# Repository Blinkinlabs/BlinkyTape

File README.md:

# BlinkyTape

BlinkyTape is a one meter long, full-color light tape with 60 independent RGB LEDs controlled by our custom light processor. Power and communications are provided by a built-in micro-USB connector. An on-board button allows for simple interactions such as choosing between effects.

BlinkyTape is flexible, so you can easily integrate it into any shape your project needs. BlinkyTape also comes enclosed in weatherproof silicone, so it's suitable for outdoor use!

This GitHub repository contains the design files for the BlinkyTape controller, as well as the production test files.

More information about the BlinkyTape is available here: [http://blinkinlabs.com/blinkytape/](http://blinkinlabs.com/blinkytape/)

# I want one!

Cool! BlinkyTape is available in [our store](http://blinkinlabs.myshopify.com/products/blinkytape-basic), as well as through many fine distributors.

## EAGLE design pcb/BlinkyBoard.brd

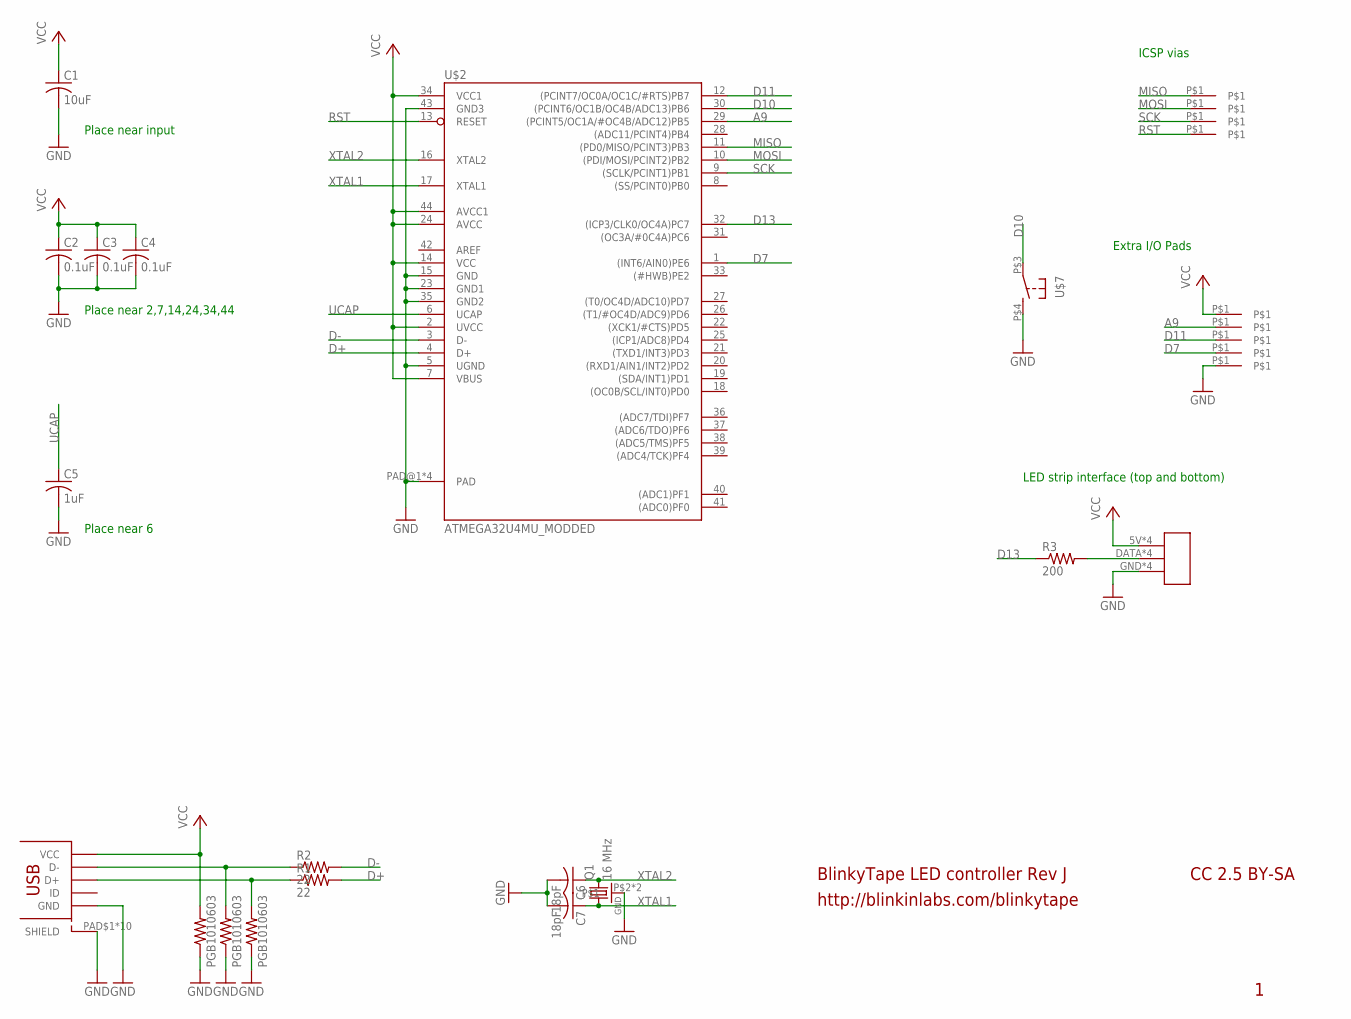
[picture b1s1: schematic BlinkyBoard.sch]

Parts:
C1: 10uF; C0603K
C2, C3, C4: 0.1uF; CAP_0402_KEMET_MEDIAN
C5: 1uF; CAP_0402_KEMET_MEDIAN
C6, C7: 18pF; CAP_0402_KEMET_MEDIAN
Q1: 16 MHz; CRSYTAL_2520
R1, R2: 22; RES_0402_KEMET_MEDIAN
R3: 200; RES_0402_KEMET_MEDIAN
U$1, U$3, U$5, U$6: TEST_PAD_SMT; TEST_PAD_1MM
U$2: ATMEGA32U4MU_MODDED; QFN44ML_7X7_LONGLEADS_MOD
U$4: USB_MICROSMT+THRUHULE; USB_MICRO_THRUHOLE
U$7: BUTTON_MOMENTARY; BUTTON_2P_SMD
U$9: WS2812B_CONNECTOR
U$10, U$11, U$12, U$13, U$14: TEST_PAD_SMT
Z1, Z2, Z3: PGB1010603; SPARKFUN-RESISTORS_0603-RES; MPN PGB1010603NRHF

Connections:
A9: U$2.29 ((PCINT5/OC1A/#OC4B/ADC12)PB5), U$11.P$1
AREF: U$2.42 (AREF)
D7: U$2.1 ((INT6/AIN0)PE6), U$10.P$1
D10: U$2.30 ((PCINT6/OC1B/OC4B/ADC13)PB6), U$7.P$3
D11: U$2.12 ((PCINT7/OC0A/OC1C/#RTS)PB7), U$14.P$1
D13: R3.P$1 (1), U$2.32 ((ICP3/CLK0/OC4A)PC7)
D+: R1.P$2 (2), U$2.4 (D+)
D+_IN: R1.P$1 (1), U$4.PIN$3 (D+), Z1.2
D-: R2.P$2 (2), U$2.3 (D-)
D-_IN: R2.P$1 (1), U$4.PIN$2 (D-), Z2.2
GND: C1.2, C2.P$2 (2), C3.P$2 (2), C4.P$2 (2), C5.P$2 (2), C6.P$2 (2), C7.P$2 (2), Q1.P$2, Q1.P$4, U$2.5 (UGND), U$2.15 (GND), U$2.23 (GND1), U$2.35 (GND2), U$2.43 (GND3), U$2.PAD@1 (PAD), U$2.PAD@4 (PAD), U$2.PAD@13 (PAD), U$2.PAD@16 (PAD), U$4.PAD$1 (SHIELD), U$4.PAD$2 (SHIELD), U$4.PAD$3 (SHIELD), U$4.PAD$4 (SHIELD), U$4.PAD$5 (SHIELD), U$4.PAD$6 (SHIELD), U$4.PAD$7 (SHIELD), U$4.PAD$8 (SHIELD), U$4.PAD$9 (SHIELD), U$4.PAD$10 (SHIELD), U$4.PIN$5 (GND), U$7.P$4 (S), U$9.GND, U$9.GND1 (GND), U$9.GND_1 (GND), U$9.GND_2 (GND), U$13.P$1, Z1.1, Z2.1, Z3.1
LED_DATA: R3.P$2 (2), U$9.DATA, U$9.DATA1 (DATA), U$9.DATA_1 (DATA), U$9.DATA_2 (DATA)
MISO: U$1.P$1, U$2.11 ((PD0/MISO/PCINT3)PB3)
MOSI: U$2.10 ((PDI/MOSI/PCINT2)PB2), U$3.P$1
RST: U$2.13 (RESET), U$6.P$1
SCK: U$2.9 ((SCLK/PCINT1)PB1), U$5.P$1
UCAP: C5.P$1 (1), U$2.6 (UCAP)
VCC: C1.1, C2.P$1 (1), C3.P$1 (1), C4.P$1 (1), U$2.2 (UVCC), U$2.7 (VBUS), U$2.14 (VCC), U$2.24 (AVCC), U$2.34 (VCC1), U$2.44 (AVCC1), U$4.PIN$1 (VCC), U$9.5V, U$9.5V1 (5V), U$9.5V_1 (5V), U$9.5V_2 (5V), U$12.P$1, Z3.2
XTAL1: C7.P$1 (1), Q1.P$1 (1), U$2.17 (XTAL1)
XTAL2: C6.P$1 (1), Q1.P$3 (2), U$2.16 (XTAL2)

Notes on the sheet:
BlinkyTape LED controller Rev J
http://blinkinlabs.com/blinkytape
CC 2.5 BY-SA
ICSP vias
Extra I/O Pads
LED strip interface (top and bottom)
Place near 6
Place near 2,7,14,24,34,44
Place near input

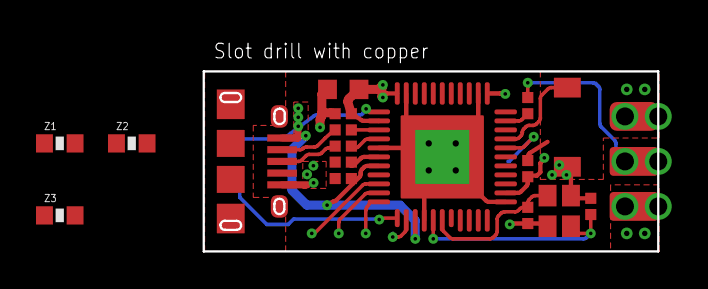
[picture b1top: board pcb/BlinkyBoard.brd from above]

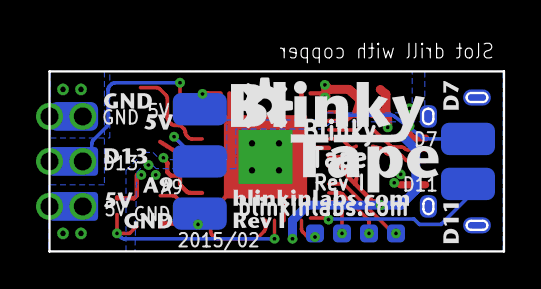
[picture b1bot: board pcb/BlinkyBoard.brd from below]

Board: 2 copper layers, 25.2 x 10.0 mm, 28 parts (11 on the bottom side), 19 nets.

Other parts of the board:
U$15: OSHW-LOGO-S

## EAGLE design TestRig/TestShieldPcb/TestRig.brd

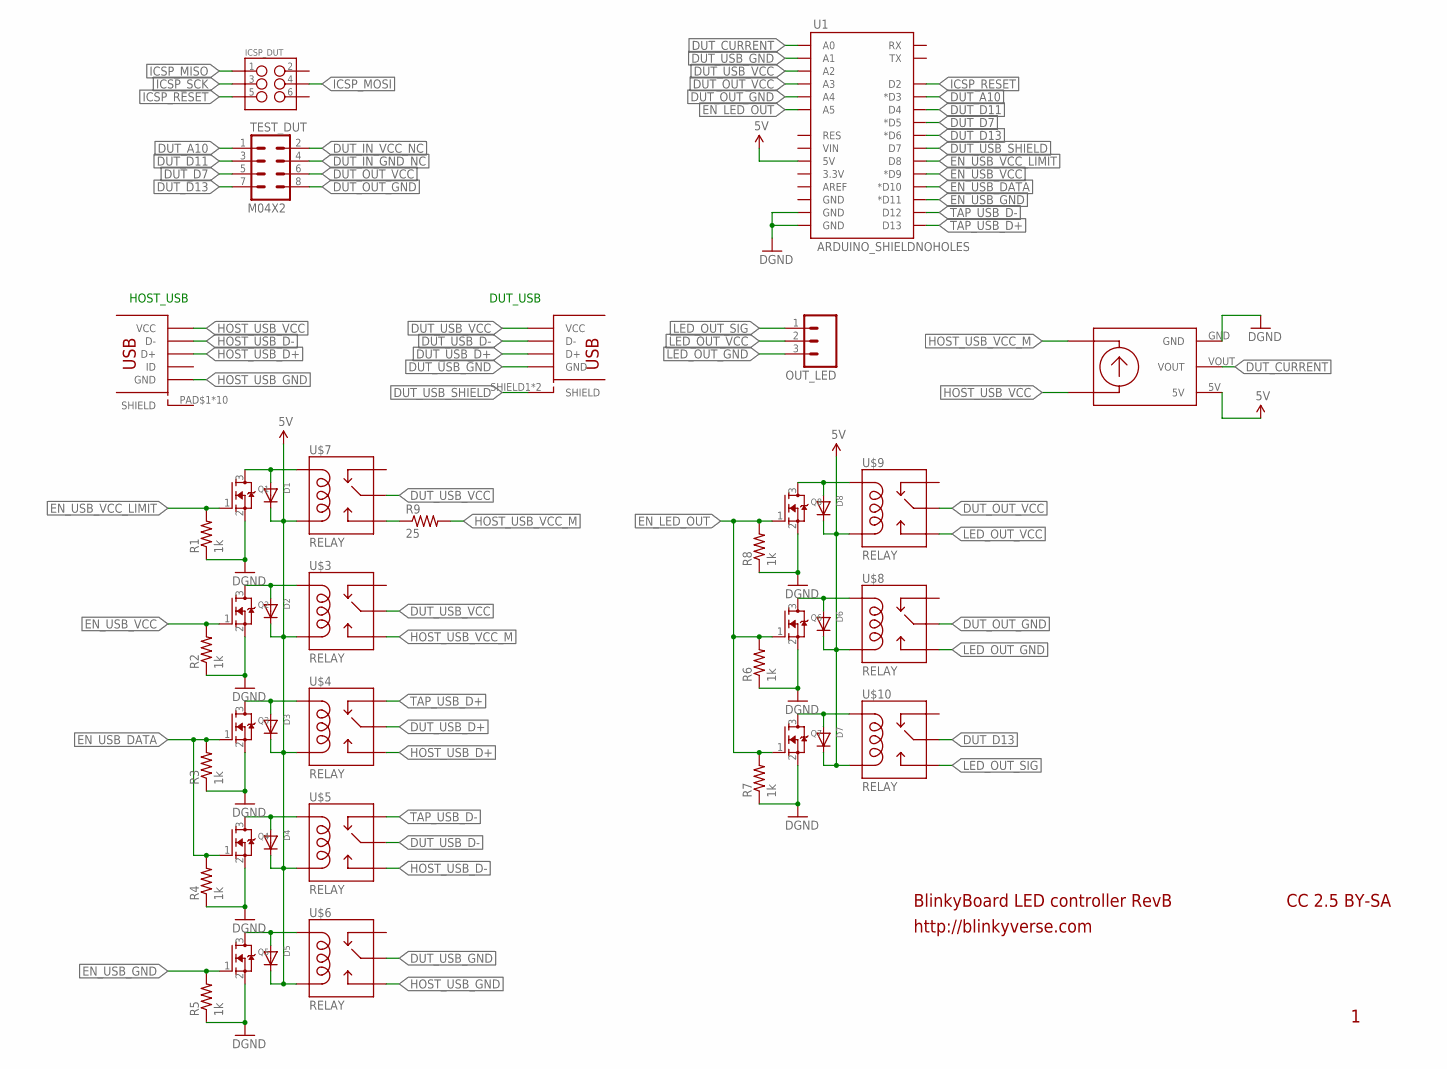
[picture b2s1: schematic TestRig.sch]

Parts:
D1, D2, D3, D4, D5, D6, D7, D8: DIODESOD-523; SOD-523
ICSP_DUT: M03X2NO_SILK; 2X3-NS
OUT_LED: M03PTH; 1X03
Q1, Q2, Q3, Q4, Q5, Q6, Q7, Q8: MOSFET-NREFLOW; SOT23
R1, R2, R3, R4, R5, R6, R7, R8: 1k; R0603
R9: 25; R1210
TEST_DUT: M04X2; 2X4
U1: ARDUINO_SHIELDNOHOLES; DUEMILANOVE_SHIELD_NOHOLES
U$1: USB; USB_A_FEMALE_NOSILK_SHIELD
U$2: MICRO_USBSMT+THRUHULE; MICRO_USB_FCI_THRUHOLE
U$3, U$4, U$5, U$6, U$7, U$8, U$9, U$10: RELAY; RELAY_HK23F-5V
U$11: SPARKFUN_ACS712

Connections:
5V: D1.K (C), D2.K (C), D3.K (C), D4.K (C), D5.K (C), D6.K (C), D7.K (C), D8.K (C), U1.5V, U$3.P$5 (COIL2), U$4.P$5 (COIL2), U$5.P$5 (COIL2), U$6.P$5 (COIL2), U$7.P$5 (COIL2), U$8.P$5 (COIL2), U$9.P$5 (COIL2), U$10.P$5 (COIL2), U$11.5V
DUT_A10: TEST_DUT.1, U1.D3 (*D3)
DUT_CURRENT: U1.A0, U$11.VOUT
DUT_D7: TEST_DUT.5, U1.D5 (*D5)
DUT_D11: TEST_DUT.3, U1.D4
DUT_D13: TEST_DUT.7, U1.D6 (*D6), U$10.P$1 (MAIN), U$10.P$6 (MAIN)
DUT_IN_GND_NC: TEST_DUT.4
DUT_IN_VCC_NC: TEST_DUT.2
DUT_OUT_GND: TEST_DUT.8, U1.A4, U$8.P$1 (MAIN), U$8.P$6 (MAIN)
DUT_OUT_VCC: TEST_DUT.6, U1.A3, U$9.P$1 (MAIN), U$9.P$6 (MAIN)
DUT_USB_D+: U$1.D+, U$4.P$1 (MAIN), U$4.P$6 (MAIN)
DUT_USB_D-: U$1.D-, U$5.P$1 (MAIN), U$5.P$6 (MAIN)
DUT_USB_GND: U1.A1, U$1.GND, U$6.P$1 (MAIN), U$6.P$6 (MAIN)
DUT_USB_SHIELD: U1.D7, U$1.SHIELD1 (SHIELD), U$1.SHIELD2 (SHIELD)
DUT_USB_VCC: U1.A2, U$1.VBUS (VCC), U$3.P$1 (MAIN), U$3.P$6 (MAIN), U$7.P$1 (MAIN), U$7.P$6 (MAIN)
EN_LED_OUT: Q6.1 (G), Q7.1 (G), Q8.1 (G), R6.2, R7.2, R8.2, U1.A5
EN_USB_DATA: Q3.1 (G), Q4.1 (G), R3.2, R4.2, U1.D10 (*D10)
EN_USB_GND: Q5.1 (G), R5.2, U1.D11 (*D11)
EN_USB_VCC: Q2.1 (G), R2.2, U1.D9 (*D9)
EN_USB_VCC_LIMIT: Q1.1 (G), R1.2, U1.D8
GND: Q1.2 (S), Q2.2 (S), Q3.2 (S), Q4.2 (S), Q5.2 (S), Q6.2 (S), Q7.2 (S), Q8.2 (S), R1.1, R2.1, R3.1, R4.1, R5.1, R6.1, R7.1, R8.1, U1.GND@0 (GND), U1.GND@1 (GND), U$11.GND
HOST_USB_D+: U$2.PIN$3 (D+), U$4.P$3 (NO)
HOST_USB_D-: U$2.PIN$2 (D-), U$5.P$3 (NO)
HOST_USB_GND: U$2.PIN$5 (GND), U$6.P$3 (NO)
HOST_USB_VCC: U$2.PIN$1 (VCC), U$11.IP-
HOST_USB_VCC_M: R9.2, U$3.P$3 (NO), U$11.IP+
ICSP_MISO: ICSP_DUT.1
ICSP_MOSI: ICSP_DUT.4
ICSP_RESET: ICSP_DUT.5, U1.D2
ICSP_SCK: ICSP_DUT.3
LED_OUT_GND: OUT_LED.3, U$8.P$3 (NO)
LED_OUT_SIG: OUT_LED.1, U$10.P$3 (NO)
LED_OUT_VCC: OUT_LED.2, U$9.P$3 (NO)
unnamed: R9.1, U$7.P$3 (NO)
unnamed: D1.A, Q1.3 (D), U$7.P$2 (COIL1)
unnamed: D2.A, Q2.3 (D), U$3.P$2 (COIL1)
unnamed: D3.A, Q3.3 (D), U$4.P$2 (COIL1)
unnamed: D4.A, Q4.3 (D), U$5.P$2 (COIL1)
unnamed: D5.A, Q5.3 (D), U$6.P$2 (COIL1)
unnamed: D6.A, Q6.3 (D), U$8.P$2 (COIL1)
unnamed: D7.A, Q7.3 (D), U$10.P$2 (COIL1)
unnamed: D8.A, Q8.3 (D), U$9.P$2 (COIL1)
TAP_USB_D+: U1.D13, U$4.P$4 (NC)
TAP_USB_D-: U1.D12, U$5.P$4 (NC)

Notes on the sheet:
BlinkyBoard LED controller RevB
http://blinkyverse.com
CC 2.5 BY-SA
DUT_USB
HOST_USB

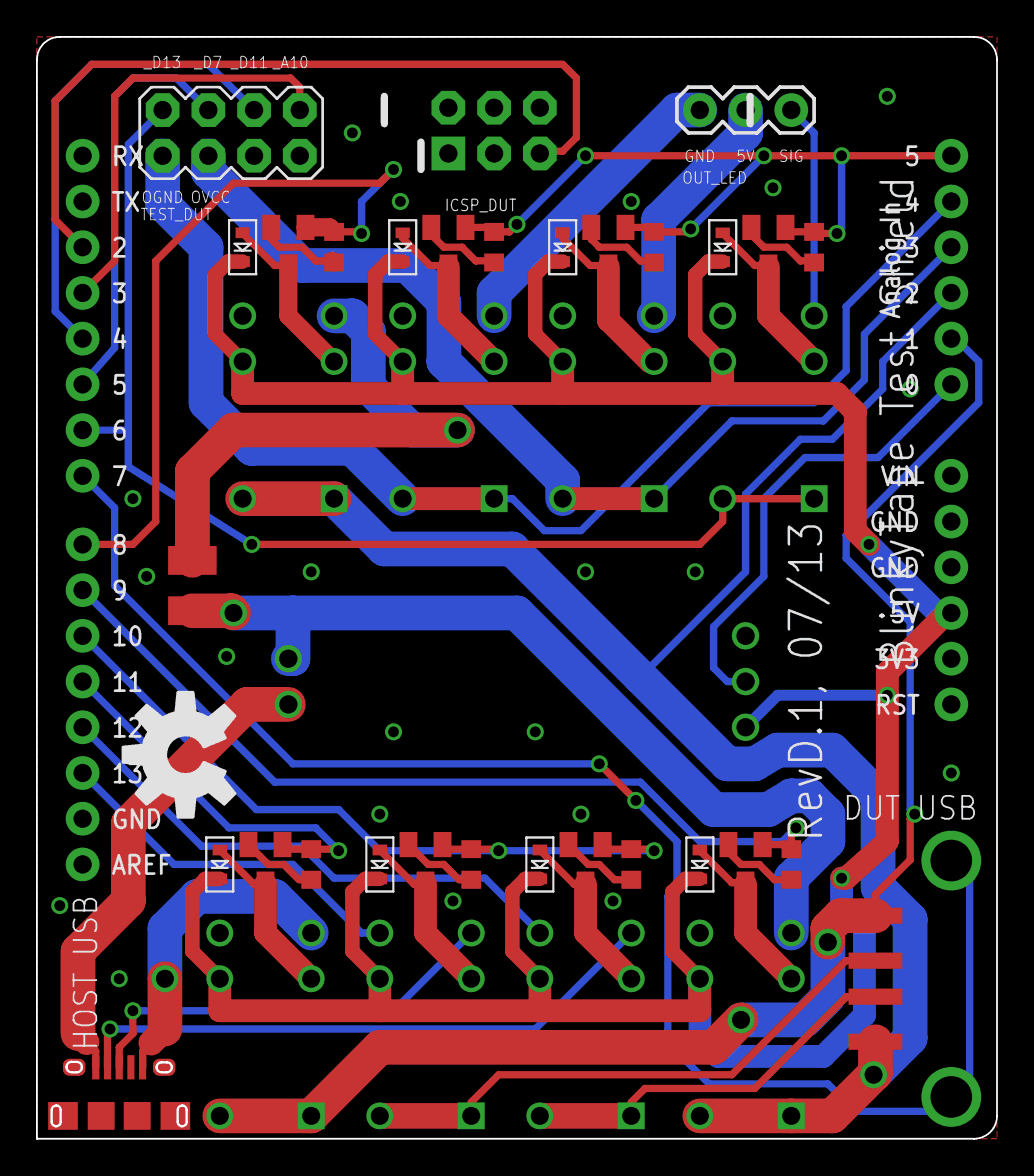
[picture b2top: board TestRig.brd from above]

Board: 2 copper layers, 53.3 x 61.2 mm, 41 parts (0 on the bottom side), 39 nets.

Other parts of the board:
U$12: OSHW-LOGO-L

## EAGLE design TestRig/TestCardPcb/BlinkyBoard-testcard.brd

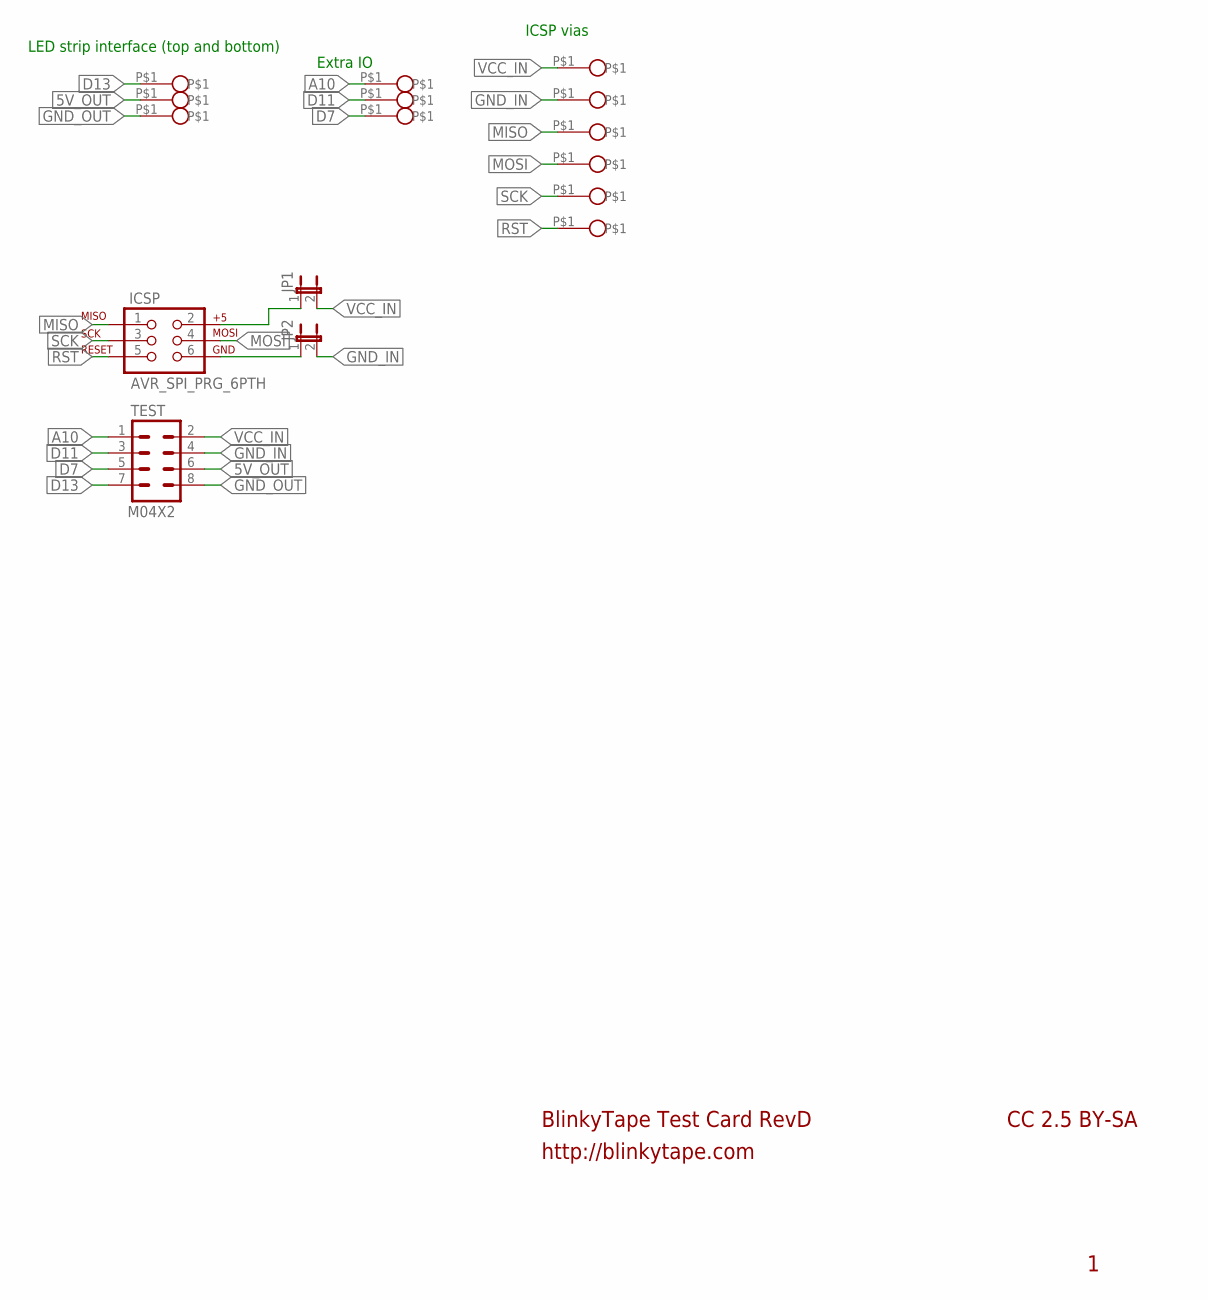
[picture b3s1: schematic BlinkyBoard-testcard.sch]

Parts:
ICSP: AVR_SPI_PRG_6PTH; 2X3
JP1, JP2: JUMPER-2PTH; 1X02
TEST: M04X2; 2X4
U$9, U$16, U$22, U$23, U$24, U$26, U$27, U$28: POGO_PIN; POGO_PIN_1MM
U$17, U$18, U$19, U$20: POGO_PINOBLONG; POGO_PIN_1MM_OBLONG

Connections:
5V_OUT: TEST.6, U$27.P$1
A10: TEST.1, U$22.P$1
D7: TEST.5, U$24.P$1
D11: TEST.3, U$23.P$1
D13: TEST.7, U$26.P$1
GND_IN: JP2.2, TEST.4, U$16.P$1
GND_OUT: TEST.8, U$28.P$1
MISO: ICSP.1, U$17.P$1
MOSI: ICSP.4, U$18.P$1
unnamed: ICSP.2, JP1.1
unnamed: ICSP.6, JP2.1
RST: ICSP.5, U$20.P$1
SCK: ICSP.3, U$19.P$1
VCC_IN: JP1.2, TEST.2, U$9.P$1

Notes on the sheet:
BlinkyTape Test Card RevD
http://blinkytape.com
CC 2.5 BY-SA
ICSP vias
LED strip interface (top and bottom)
Extra IO

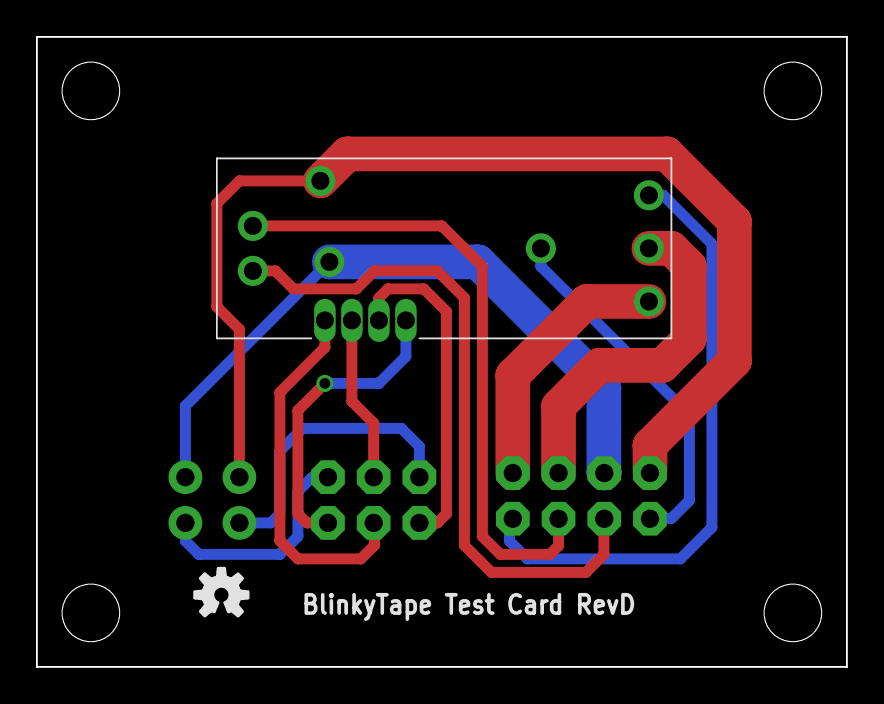
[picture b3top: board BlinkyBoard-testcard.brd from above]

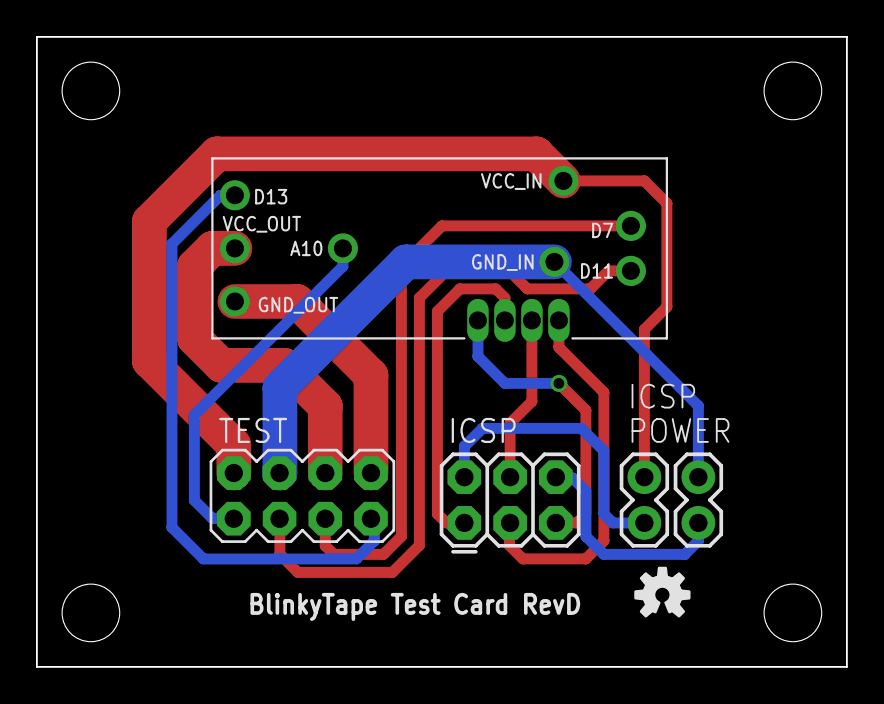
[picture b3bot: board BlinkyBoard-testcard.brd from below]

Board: 2 copper layers, 45.0 x 35.0 mm, 18 parts (5 on the bottom side), 14 nets.

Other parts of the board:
U$3, U$15: OSHW-LOGO-S

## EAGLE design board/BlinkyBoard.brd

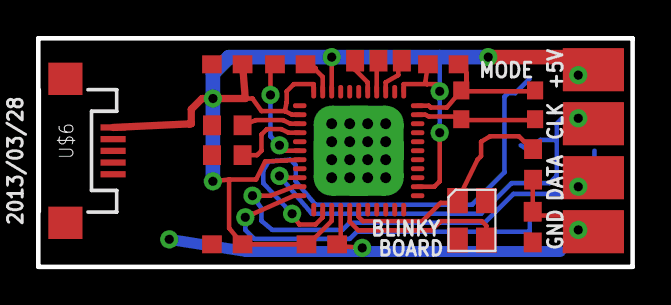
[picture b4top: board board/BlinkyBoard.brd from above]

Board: 2 copper layers, 33.0 x 12.7 mm, 17 parts (0 on the bottom side), 17 nets.

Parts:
C1: 1uF; C0603
C2, C3: 18pF; C0603
C4, C6, C7, C8: 0.1uF; C0603
Q1: 16 MHz; XS3225
R1, R2: 22; R0603
S1: Normally open; GLOWBOARD_KMR211G_SWITCH
U$1: ARDUINO_LEONARDO-REV3B_SMARTPRJ_ATMEGA32U4-XUMU; ARDUINO_LEONARDO-REV3B_SMARTPRJ_QFN44ML7X7
U$2: GLOWBOARD_USB_TEST_PADS
U$3: GLOWBOARD_PAD_CONNECTION
U$4: GLOWBOARD_ICSP; GLOWBOARD_ICSP_PADS
U$5: GLOWBOARD_EXPANSION_HEADER
U$6: USB-MICROB

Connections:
+3V3: C1.1, U$1.6
D+: R2.2, U$1.4
D+_IN: R2.1, U$2.D+, U$6.D+
D-: R1.2, U$1.3
D-_IN: R1.1, U$2.D-, U$6.D-
GND: C1.2, C2.2, C3.2, C4.2, C6.2, C7.2, C8.2, S1.P$1, S1.P$2, U$1.5, U$1.15, U$1.23, U$1.33, U$1.35, U$1.43, U$1.PAD@1, U$1.PAD@2, U$1.PAD@3, U$1.PAD@4, U$1.PAD@5, U$1.PAD@6, U$1.PAD@7, U$1.PAD@8, U$1.PAD@9, U$1.PAD@10, U$1.PAD@11, U$1.PAD@12, U$1.PAD@13, U$1.PAD@14, U$1.PAD@15, U$1.PAD@16, U$3.GND, U$4.GND, U$6.GND
MISO: U$1.11, U$4.MISO
MOSI: U$1.10, U$3.DATA, U$4.MOSI
unnamed: U$1.38, U$5.P$1
unnamed: U$1.37, U$5.P$2
unnamed: U$1.36, U$5.P$3
unnamed: C2.1, Q1.P$3, U$1.16
unnamed: C3.1, Q1.P$1, U$1.17
unnamed: S1.P$3, S1.P$4, U$1.32
RST: U$1.13, U$4.RST
SCK: U$1.9, U$3.CLK, U$4.SCK
VCC: C4.1, C6.1, C7.1, C8.1, U$1.2, U$1.7, U$1.14, U$1.24, U$1.34, U$1.42, U$1.44, U$3.+5V, U$4.VCC, U$6.VBUS

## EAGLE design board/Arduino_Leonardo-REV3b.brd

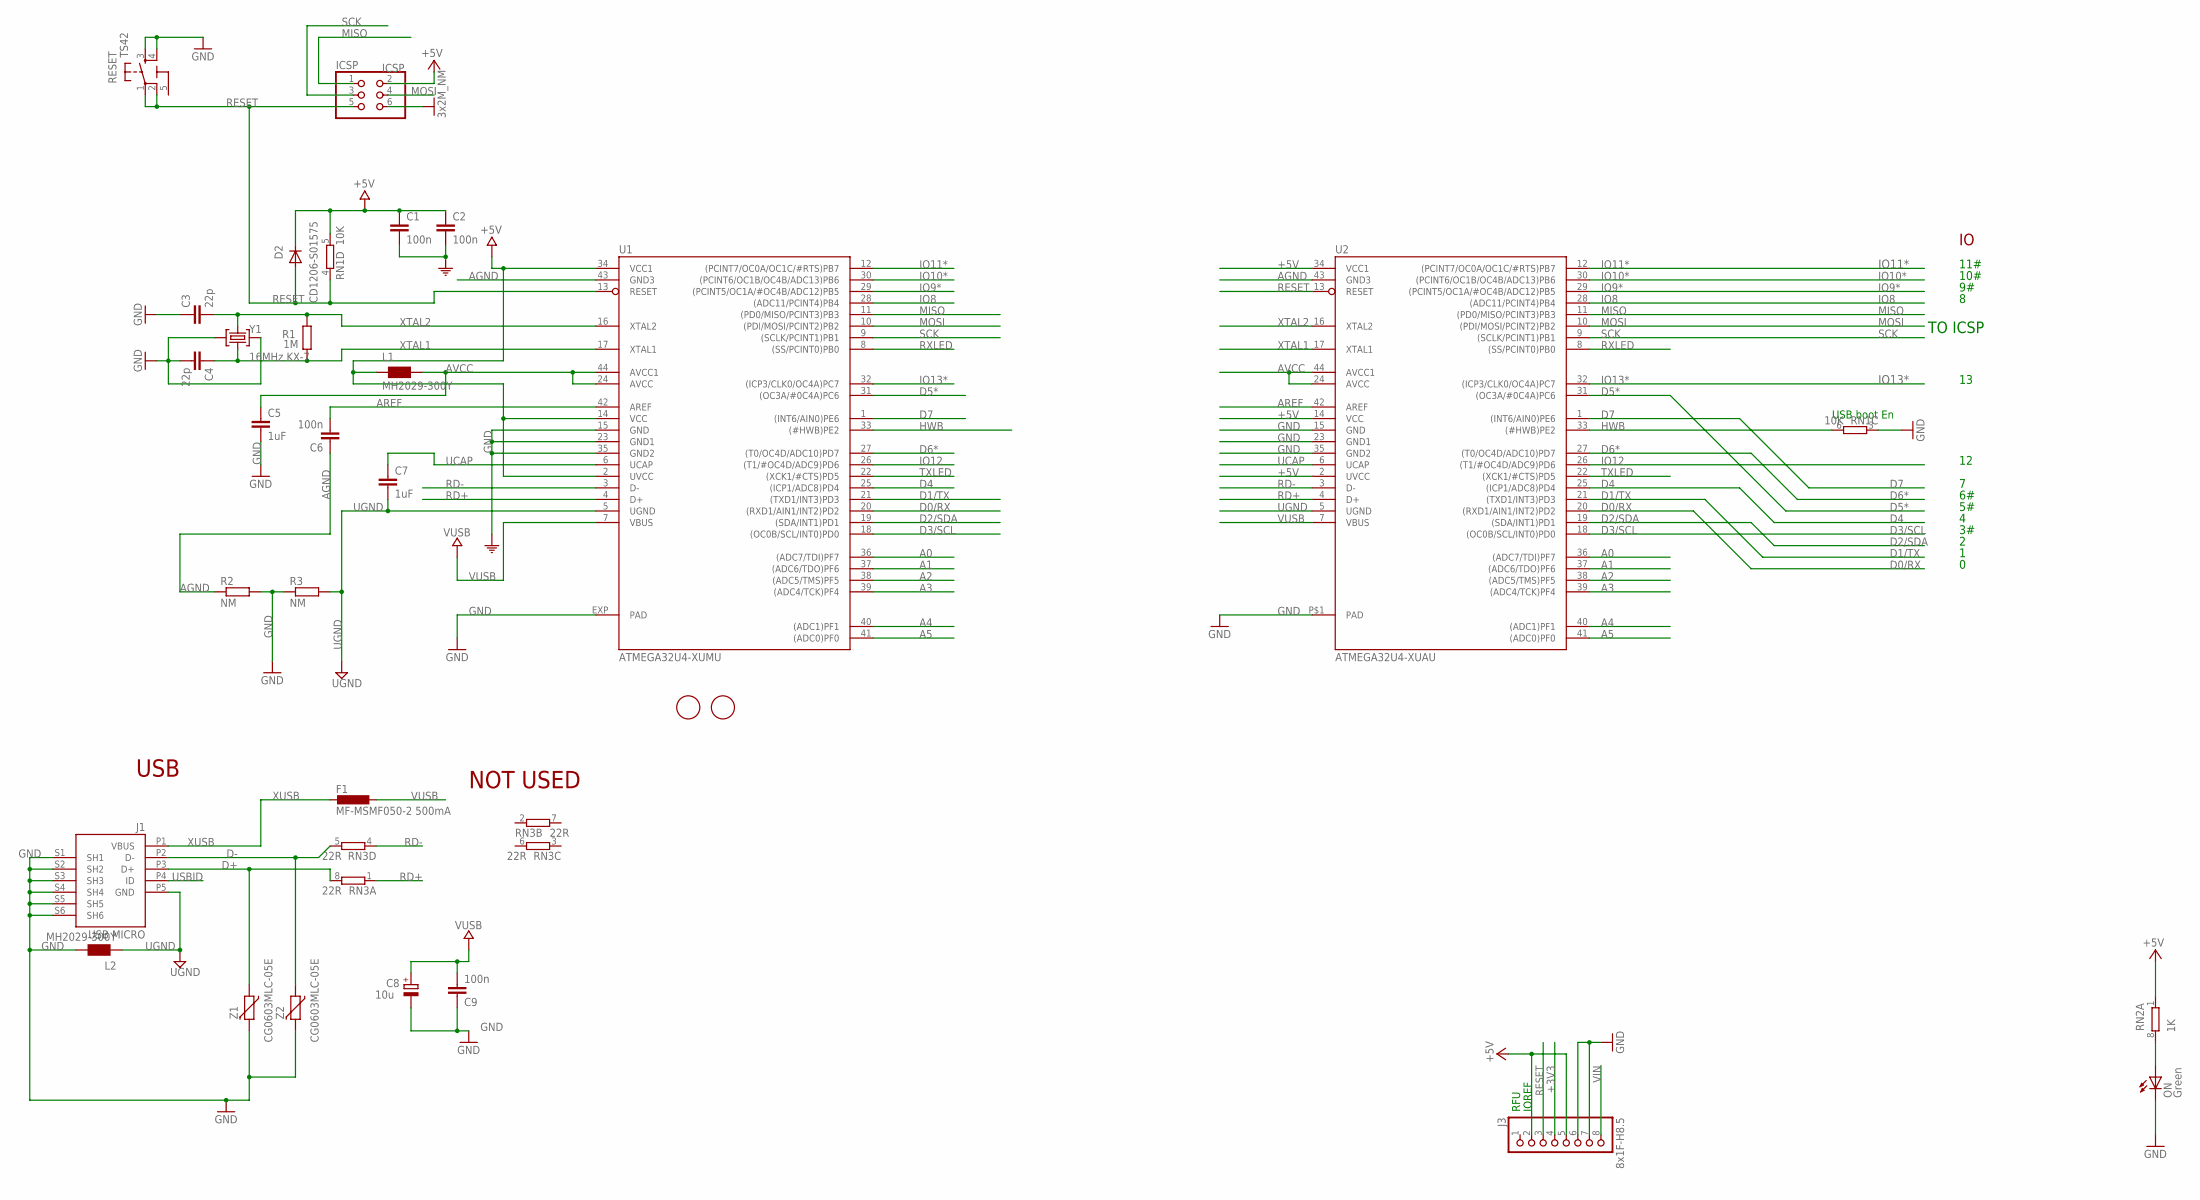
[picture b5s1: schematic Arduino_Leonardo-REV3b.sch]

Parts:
C1, C2, C6, C9: 100n; C0603-ROUND
C3, C4: 22p; C0603-ROUND
C5, C7: 1uF; C0603-ROUND
C8: 10u; SMC_B
D2: CD1206-S01575; MINIMELF
F1: MF-MSMF050-2 500mA; L1812
FID1, FID2: FIDUCIALMOUNT; FIDUCIA-MOUNT
ICSP: ICSP; 2X03
J1: USB MICRO; CON2_USB_MICRO_B_AT
J3: 8x1F-H8.5; 1X08
L1, L2: MH2029-300Y; 0805
ON: Green; CHIPLED_0805
R1: 1M; R0603-ROUND
R2, R3: NM; R0402
RESET: TS42
RN1: 10K; CAY16
RN2: 1K; CAY16
RN3: 22R; CAY16
U1: ATMEGA32U4-XUMU; QFN44ML7X7
U2: ATMEGA32U4-XUAU; TQFP44-PAD
Y1: 16MHz KX-7; CRYSTAL-3.2-2.5
Z1, Z2: CG0603MLC-05E; CT/CN0603

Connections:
5-GND: RESET.5 (5-GND)
+3V3: J3.4
+5V: C1.1, C2.1, D2.C, ICSP.2, J3.2, J3.5, L1.1, RN1.5 (2), RN2.1, U1.2 (UVCC), U1.14 (VCC), U1.34 (VCC1), U2.2 (UVCC), U2.14 (VCC), U2.34 (VCC1)
A0: U1.36 ((ADC7/TDI)PF7), U2.36 ((ADC7/TDI)PF7)
A1: U1.37 ((ADC6/TDO)PF6), U2.37 ((ADC6/TDO)PF6)
A2: U1.38 ((ADC5/TMS)PF5), U2.38 ((ADC5/TMS)PF5)
A3: U1.39 ((ADC4/TCK)PF4), U2.39 ((ADC4/TCK)PF4)
A4: U1.40 ((ADC1)PF1), U2.40 ((ADC1)PF1)
A5: U1.41 ((ADC0)PF0), U2.41 ((ADC0)PF0)
AGND: C6.1, R2.1, U1.43 (GND3), U2.43 (GND3)
AREF: C6.2, U1.42 (AREF), U2.42 (AREF)
AVCC: C5.1, L1.2, U1.24 (AVCC), U1.44 (AVCC1), U2.24 (AVCC), U2.44 (AVCC1)
D0/RX: U1.20 ((RXD1/AIN1/INT2)PD2), U2.20 ((RXD1/AIN1/INT2)PD2)
D1/TX: U1.21 ((TXD1/INT3)PD3), U2.21 ((TXD1/INT3)PD3)
D2/SDA: U1.19 ((SDA/INT1)PD1), U2.19 ((SDA/INT1)PD1)
D3/SCL: U1.18 ((OC0B/SCL/INT0)PD0), U2.18 ((OC0B/SCL/INT0)PD0)
D4: U1.25 ((ICP1/ADC8)PD4), U2.25 ((ICP1/ADC8)PD4)
D5*: U1.31 ((OC3A/#0C4A)PC6), U2.31 ((OC3A/#0C4A)PC6)
D6*: U1.27 ((T0/OC4D/ADC10)PD7), U2.27 ((T0/OC4D/ADC10)PD7)
D7: U1.1 ((INT6/AIN0)PE6), U2.1 ((INT6/AIN0)PE6)
D+: J1.P3 (D+), RN3.8 (2), Z1.1
D-: J1.P2 (D-), RN3.5 (2), Z2.1
GND: C1.2, C2.2, C3.1, C4.2, C5.2, C8.-, C9.1, ICSP.6, J1.S1 (SH1), J1.S2 (SH2), J1.S3 (SH3), J1.S4 (SH4), J1.S5 (SH5), J1.S6 (SH6), J3.6, J3.7, L2.2, ON.C, R2.2, R3.1, RESET.3, RESET.4, RN1.3 (1), U1.15 (GND), U1.23 (GND1), U1.35 (GND2), U1.EXP (PAD), U2.15 (GND), U2.23 (GND1), U2.35 (GND2), U2.P$1 (PAD), Y1.2 (GND), Y1.4 (GND), Z1.2, Z2.2
HWB: RN1.6 (2), U1.33 ((#HWB)PE2), U2.33 ((#HWB)PE2)
IO8: U1.28 ((ADC11/PCINT4)PB4), U2.28 ((ADC11/PCINT4)PB4)
IO9*: U1.29 ((PCINT5/OC1A/#OC4B/ADC12)PB5), U2.29 ((PCINT5/OC1A/#OC4B/ADC12)PB5)
IO10*: U1.30 ((PCINT6/OC1B/OC4B/ADC13)PB6), U2.30 ((PCINT6/OC1B/OC4B/ADC13)PB6)
IO11*: U1.12 ((PCINT7/OC0A/OC1C/#RTS)PB7), U2.12 ((PCINT7/OC0A/OC1C/#RTS)PB7)
IO12: U1.26 ((T1/#OC4D/ADC9)PD6), U2.26 ((T1/#OC4D/ADC9)PD6)
IO13*: U1.32 ((ICP3/CLK0/OC4A)PC7), U2.32 ((ICP3/CLK0/OC4A)PC7)
MISO: ICSP.1, U1.11 ((PD0/MISO/PCINT3)PB3), U2.11 ((PD0/MISO/PCINT3)PB3)
MOSI: ICSP.4, U1.10 ((PDI/MOSI/PCINT2)PB2), U2.10 ((PDI/MOSI/PCINT2)PB2)
unnamed: ON.A, RN2.8 (2)
RD+: RN3.1, U1.4 (D+), U2.4 (D+)
RD-: RN3.4 (1), U1.3 (D-), U2.3 (D-)
RESET: D2.A, ICSP.5, J3.3, RESET.1, RESET.2, RN1.4 (1), U1.13 (RESET), U2.13 (RESET)
RXLED: U1.8 ((SS/PCINT0)PB0), U2.8 ((SS/PCINT0)PB0)
SCK: ICSP.3, U1.9 ((SCLK/PCINT1)PB1), U2.9 ((SCLK/PCINT1)PB1)
TXLED: U1.22 ((XCK1/#CTS)PD5), U2.22 ((XCK1/#CTS)PD5)
UCAP: C7.1, U1.6 (UCAP), U2.6 (UCAP)
UGND: C7.2, J1.P5 (GND), L2.1, R3.2, U1.5 (UGND), U2.5 (UGND)
USBID: J1.P4 (ID)
VIN: J3.8
VUSB: C8.+, C9.2, F1.1, U1.7 (VBUS), U2.7 (VBUS)
XTAL1: C4.1, R1.1, U1.17 (XTAL1), U2.17 (XTAL1), Y1.1 (C1)
XTAL2: C3.2, R1.2, U1.16 (XTAL2), U2.16 (XTAL2), Y1.3 (C2)
XUSB: F1.2, J1.P1 (VBUS)

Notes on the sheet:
USB boot En
USB
NOT USED
TO ICSP
10#
11#
IOREF
RFU

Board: 2 copper layers, 31 parts (2 on the bottom side), 43 nets, no tracks yet.

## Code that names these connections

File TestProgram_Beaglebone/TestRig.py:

import time

import DetectPlatform
import RemoteArduino



class ArduinoPin:
  def __init__(self, name, number, net = None, suppressHigh = False, suppressLow = False):
    self.name = name
    self.number = number

    if(net == None):
      self.net = name
    else:
      self.net = net

    self.suppressHigh = suppressHigh
    self.suppressLow = suppressLow

  def __str__(self):
    return self.name

class MeasurementPin():
  def __init__(self, name, number, M, B):
    self.name = name
    self.number = number
    self.M = M
    self.B = B

  def __str__(self):
    return self.name


class TestRig:
  """ Class that represents a BlinkyTape test rig"""

  def __init__(self, port, measurementPins, relayPins, shortTestPins):
    self.measurementPins = measurementPins
    self.relayPins = relayPins
    self.shortTestPins = shortTestPins

    # TODO: don't connect here?
    self.connect(port)

  def connect(self, port):
    """Initialize a connection to a test rig"""
    self.port = port
    self.arduino = RemoteArduino.RemoteArduino(port)
    remoteVersion = self.arduino.getRemoteVersion()
    if remoteVersion < 1:
      raise Exception("Remote version (" + hex(remoteVersion) + ") too low, upgrade the Arduino sketch")

    self.resetState()

  def disconnect(self):
    self.arduino = None

  def resetState(self):
    """ Set all relay pins to output and low, and all short test pins to high-impedance inputs """
    for pin in self.relayPins:
      self.arduino.digitalWrite(pin.number, 'LOW')
      self.arduino.pinMode(pin.number, 'OUTPUT')

    for pin in self.shortTestPins:
      self.arduino.pinMode(pin.number, 'INPUT')

    # TODO: reset analog pins?

  def enableRelay(self, relayName):
    """ Enable an output relay """
    for pin in self.relayPins:
      if pin.name == relayName:
        self.arduino.digitalWrite(pin.number, 'HIGH')
        return
    raise Exception("Relay " + relayName + "not found!")
    
  def disableRelay(self, relayName):
    """ Disable an output relay """
    for pin in self.relayPins:
      if pin.name == relayName:
        self.arduino.digitalWrite(pin.number, 'LOW')
        return
    raise Exception("Relay " + relayName + "not found!")

  def setOutputLow(self, pinName):
    """ Disable an output relay """
    for pin in self.shortTestPins:
      if pin.name == pinName:
        self.arduino.pinMode(pin.number, 'OUTPUT')
        self.arduino.digitalWrite(pin.number, 'LOW')
        return
    raise Exception("Pin" + pinName + "not found!")

  def setOutputHigh(self, pinName):
    """ Disable an output relay """
    for pin in self.shortTestPins:
      if pin.name == pinName:
        self.arduino.pinMode(pin.number, 'OUTPUT')
        self.arduino.digitalWrite(pin.number, 'HIGH')
        return
    raise Exception("Pin" + pinName + "not found!")

  def setInput(self, pinName):
    """ Set up a pin as input"""
    for pin in self.shortTestPins:
      if pin.name == pinName:
        self.arduino.pinMode(pin.number, 'INPUT')
        return
    raise Exception("Pin" + pinName + "not found!")

  def setInputPullup(self, pinName):
    """ Set up a pin as input in pullup mode"""
    for pin in self.shortTestPins:
      if pin.name == pinName:
        self.arduino.pinMode(pin.number, 'INPUT_PULLUP')
        return
    raise Exception("Pin" + pinName + "not found!")

  def readInput(self, pinName):
    """ Set up a pin as input in pullup mode"""
    for pin in self.shortTestPins:
      if pin.name == pinName:
        return self.arduino.digitalRead(pin.number)
    raise Exception("Pin" + pinName + "not found!")

  def setProgrammerSpeed(self, speed):
    """ Set the speed of the programmer"""
    return self.arduino.setProgrammerSpeed(speed)
    
  def measure(self, measurementName):
    """ Read a measurement pin """
    for pin in self.measurementPins:
      if pin.name == measurementName:
        return pin.M*(self.arduino.analogRead(pin.number) + pin.B)

    raise Exception("Measurement pin " + measurementName + "not found!")

  def shortTest(self, pinName):
    """ Perform a short test between the given pin and all other pins by pulling the given pin low,
        then each other pin high using a weak pull-up, and measuring the other pin
    """
    faults = []

    # Step through each pin, setting it as a low output, then reading in the value of all other pins
    for pin in self.shortTestPins:
      if pin.name != pinName:
        continue

      # Short everything together by setting it to high output, to discharge passives
      for p in self.shortTestPins:
        self.arduino.pinMode(p.number, 'OUTPUT')
        self.arduino.digitalWrite(p.number, 'LOW')
      time.sleep(.2)

      # Reset all pins to inputs
      for p in self.shortTestPins:
        self.arduino.pinMode(p.number, 'INPUT_PULLUP')

      # Set the left-side pin to low output
      self.arduino.pinMode(pin.number, 'OUTPUT')
      self.arduino.digitalWrite(pin.number, 'LOW')


      # Now, iterate through all the other pins
      # There are a few cases here:
      # - If neither pin nor inputPin are suppressHigh nor suppressLow, test them against each other.
      # - If pin is suppresslow or inputPin is suppresshigh, only test if they are on the same net.
      for inputPin in self.shortTestPins:
        if pin.name != inputPin.name:
          if (pin.suppressLow or inputPin.suppressHigh) and (pin.net != inputPin.net):
            continue

          shorted = (0 == self.arduino.digitalRead(inputPin.number))
          expectedShorted = (inputPin.net == pin.net)

          if shorted != expectedShorted:
            faults.append((pin.name, inputPin.name, expectedShorted, shorted))
   
    return sorted(list(dict.fromkeys(faults)))

def MakeDefaultRig():
  """ Actually we only have one version of the hardware. Make a class instance to represent it.
  """
  serialPorts = DetectPlatform.ListSerialPorts()
  port = serialPorts[0]

  # List of pins that are connected to analog sensors on the board
  measurementPins = [
    MeasurementPin('DUT_CURRENT',0, 1, 0),  # Note: an analog pin! Values determined by experiment
    ]

  # List of pins that control a relay on the test rig
  relayPins = [
    ArduinoPin('EN_USB_VCC_LIMIT', 8),
    ArduinoPin('EN_USB_VCC',       9),
    ArduinoPin('EN_USB_DATA',     10),
    ArduinoPin('EN_USB_GND',      11),
    ArduinoPin('EN_LED_OUT',      23),
    ]
  

  # List of pins that are connected directly to an I/O pin on the DUT,
  # that should be used to do an n*n short test
  # For nodes with reverse protection diodes (eg, VCC and GND), specifcy
  # 'suppressHigh' to prevent them from being pulled higher than any other
  # nets, and 'suppressLow' to prevent them from being pulled lower than any
  # other nets.
  shortTestPins = [
    ArduinoPin('DUT_USB_GND',    19, net='GND', suppressHigh=True), # Analog input pins as digital, A0 = 18, A1 = 19, etc
    ArduinoPin('DUT_OUT_GND',    22, net='GND', suppressHigh=True),
    ArduinoPin('DUT_USB_VCC',    20, net='VCC', suppressLow=True),
    ArduinoPin('DUT_OUT_VCC',    21, net='VCC', suppressLow=True),
    ArduinoPin('ICSP_RESET',      0),  # Regular digital pins
    ArduinoPin('DUT_A9',          1),
    # 2,3 used by I2C port for current sensor
    ArduinoPin('DUT_D11',         4),
    ArduinoPin('DUT_D7',          5),
    ArduinoPin('DUT_D13',         6),
    ArduinoPin('DUT_USB_SHIELD',  7),
    ArduinoPin('TAP_USB_D-',     12),
    ArduinoPin('TAP_USB_D+',     13),
    ArduinoPin('ICSP_MISO',      14),   # ICSP pins
    ArduinoPin('ICSP_SCK',       15),
    ArduinoPin('ICSP_MOSI',      16),
    ]
  

  return TestRig(port, measurementPins, relayPins, shortTestPins)


testRig = MakeDefaultRig()

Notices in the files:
parts and their libraries:
SparkFun-Connectors: Licensing: CC v3.0 Share-Alike You are welcome to use this library for commercial purposes.
